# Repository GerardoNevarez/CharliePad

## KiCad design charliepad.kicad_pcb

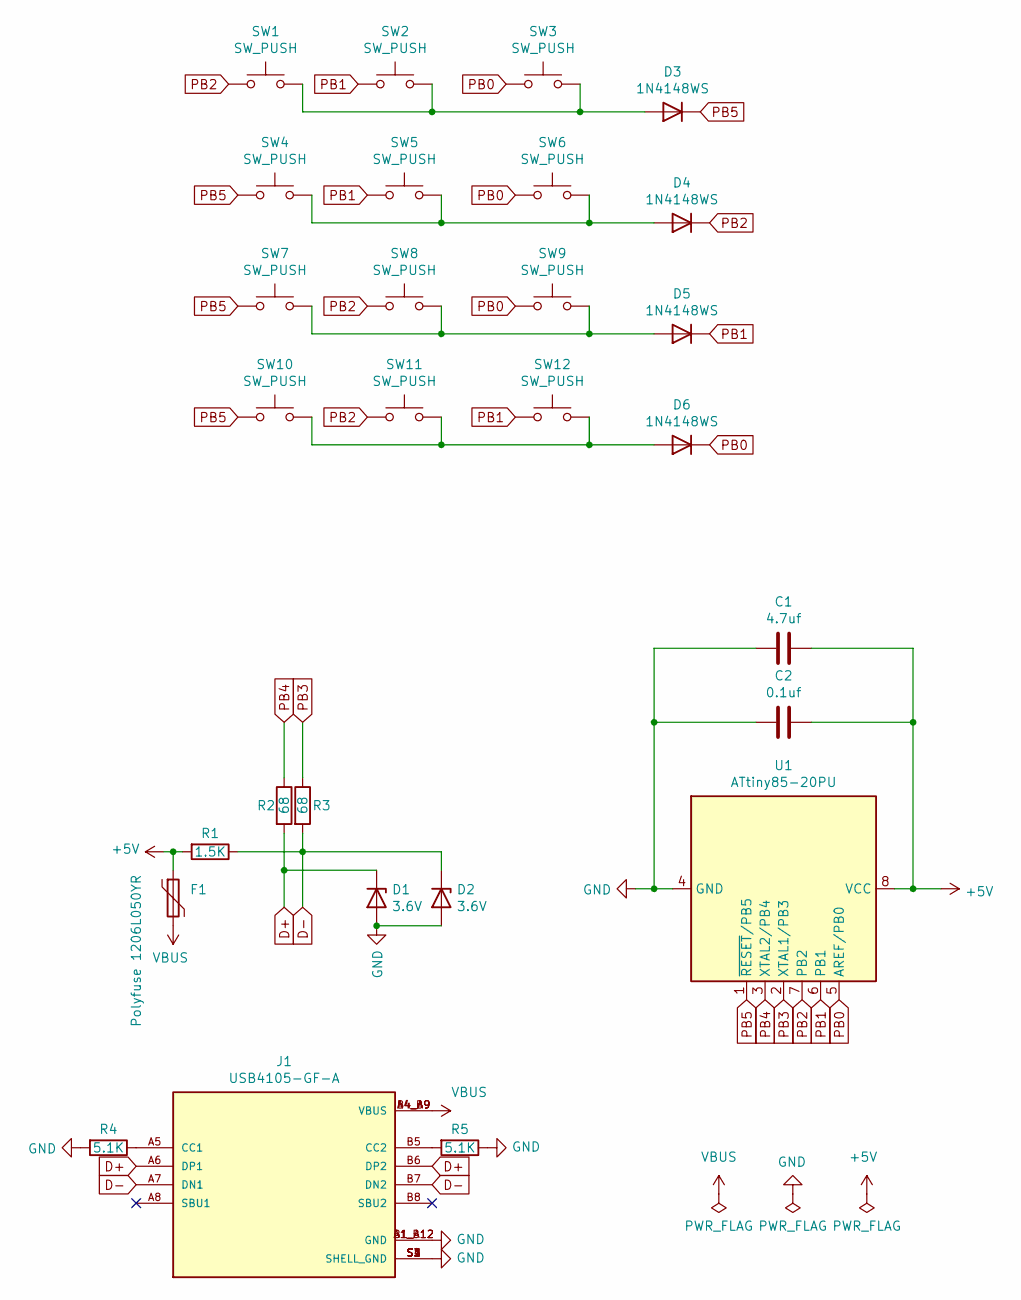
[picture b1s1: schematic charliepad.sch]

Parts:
C1: 4.7uf; C_0805_2012Metric_Pad1.18x1.45mm_HandSolder
C2: 0.1uf; C_0805_2012Metric_Pad1.18x1.45mm_HandSolder
D1, D2: 3.6V; D_SOD-123
D3, D4, D5, D6: 1N4148WS; D_SOD-323
F1: Polyfuse 1206L050YR; PTC_1206
J1: USB4105-GF-A; GCT_USB4105-GF-A; PARTREV A3
R1: 1.5K; R_0805_2012Metric_Pad1.20x1.40mm_HandSolder
R2, R3: 68; R_0805_2012Metric_Pad1.20x1.40mm_HandSolder
R4, R5: 5.1K; R_0805_2012Metric_Pad1.20x1.40mm_HandSolder
SW1, SW2, SW3, SW4, SW5, SW6, SW7, SW8, SW9, SW10, SW11, SW12: SW_PUSH; SW_PG1350_single_b2
U1: ATtiny85-20PU; DIP-8_W7.62mm

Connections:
+5V: C1.1, C2.1, F1.1, R1.2, U1.8 (VCC)
D+: D1.1 (K), J1.A6 (DP1), J1.B6 (DP2), R2.2
D-: D2.1 (K), J1.A7 (DN1), J1.B7 (DN2), R1.1, R3.2
GND: C1.2, C2.2, D1.2 (A), D2.2 (A), J1.A1_B12 (GND), J1.B1_A12 (GND), J1.S1 (SHELL_GND), J1.S2 (SHELL_GND), J1.S3 (SHELL_GND), J1.S4 (SHELL_GND), R4.2, R5.1, U1.4 (GND)
unnamed: D3.2 (A), SW1.2, SW2.2, SW3.2
unnamed: D4.2 (A), SW4.2, SW5.2, SW6.2
unnamed: D5.2 (A), SW7.2, SW8.2, SW9.2
unnamed: D6.2 (A), SW10.2, SW11.2, SW12.2
unnamed: J1.A5 (CC1), R4.1
unnamed: J1.B5 (CC2), R5.2
PB0: D6.1 (K), SW3.1, SW6.1, SW9.1, U1.5 (AREF/PB0)
PB1: D5.1 (K), SW2.1, SW5.1, SW12.1, U1.6 (PB1)
PB2: D4.1 (K), SW1.1, SW8.1, SW11.1, U1.7 (PB2)
PB3: R3.1, U1.2 (XTAL1/PB3)
PB4: R2.1, U1.3 (XTAL2/PB4)
PB5: D3.1 (K), SW4.1, SW7.1, SW10.1, U1.1 (~RESET~/PB5)
VBUS: F1.2, J1.A4_B9 (VBUS), J1.B4_A9 (VBUS)

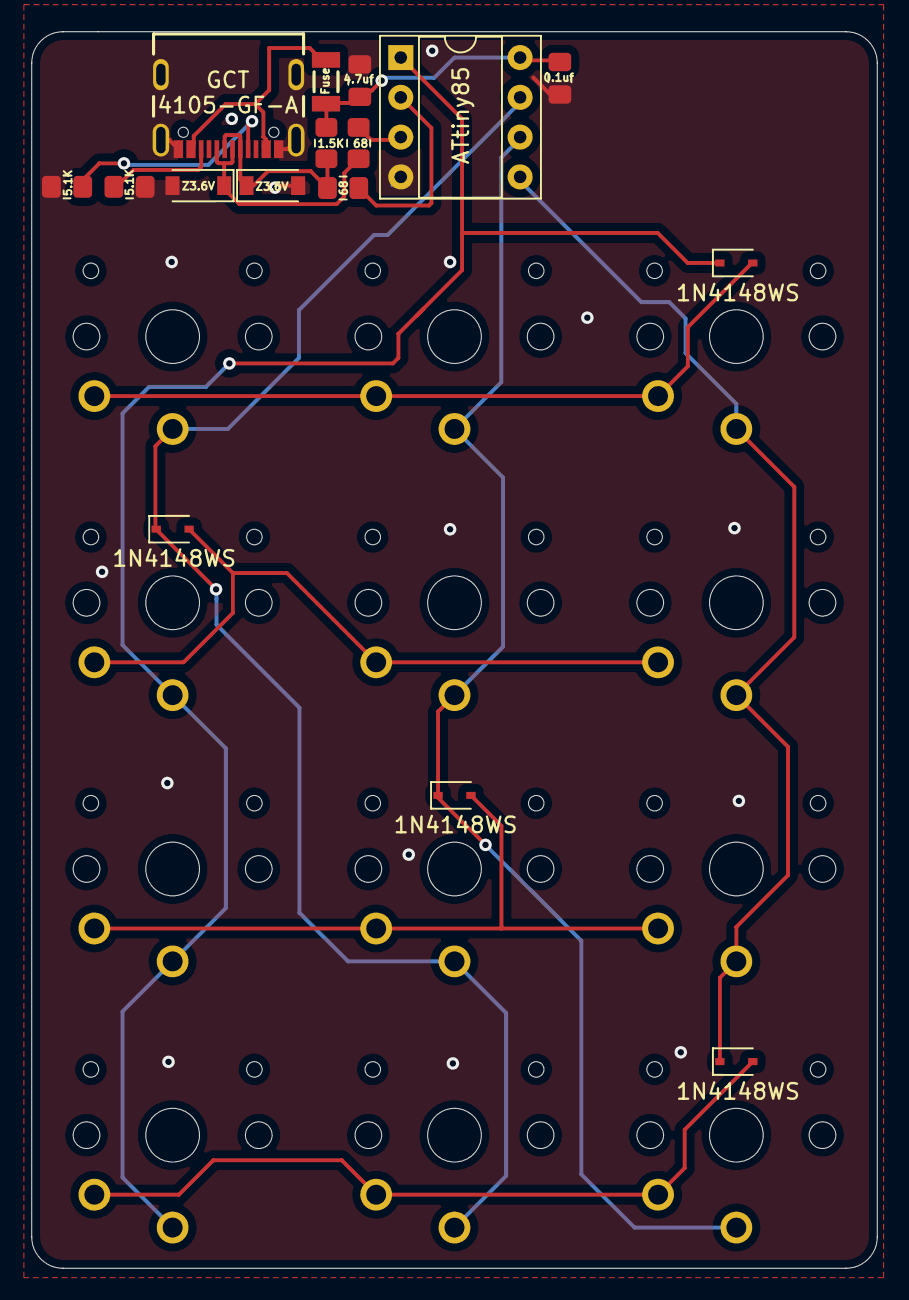
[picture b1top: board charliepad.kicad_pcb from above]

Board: 2 copper layers, 54.0 x 79.0 mm, 28 parts (0 on the bottom side), 17 nets.

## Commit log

2021-08-23 Add library files
2021-08-23 Fix USB-C link to STEP file
2024-03-26 Regularize track width Re-layout all the things, add logos, simple fw
2024-03-26 Add LICENSE
